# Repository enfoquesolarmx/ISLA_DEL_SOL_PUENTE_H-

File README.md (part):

# Isla del Sol — Puente H SPWM 48 V → 127 V / 60 Hz

Inversor / cargador de **puente H con modulación SPWM** para sistemas solares aislados: **48 V de batería → 127 V / 60 Hz, 1000 W**, con modo cargador de **1 kVA**.

El proyecto se publica como **referencia de estudio**: cada decisión de diseño está justificada y documentada (cálculos, hojas de datos, errores encontrados y cómo se corrigieron).

> ⚠️ **Advertencia de seguridad:** este equipo maneja corrientes altas en el lado de 48 V y **127 V AC en la salida, que pueden ser mortales**. Es un prototipo en desarrollo, no un producto certificado. Úsalo bajo tu propio riesgo y solo si tienes experiencia con electrónica de potencia.

---

*Tarjeta de potencia del puente H, prototipo de trinchera V0.1 (render 3D de KiCad). Detalles en [`hardware/puente_h/`](hardware/puente_h/README.md).*

*Tarjeta de transferencia de carga V0.1 (render 3D de KiCad): red / inversor / cargador con 5 relés y unión N–PE automática. Detalles en [`hardware/transferencia_reles/`](hardware/transferencia_reles/README.md).*

## Características principales

| Parámetro | Valor |
| --- | --- |
| Entrada | Batería de 48 V |
| Salida | 127 V / 60 Hz, 1000 W (transformador compatible 24–28 V / 120 V) |
| Modo inversor | Modulación híbrida: rama A a 24 kHz, rama B a 60 Hz |
| Modo cargador | Unipolar, ambas ramas a 24 kHz, 1 kVA |
| MOSFET | Infineon IRF100P219 (100 V), disipador Fischer SK 129 |
| Capacitores de bus | 4 × Rubycon 100ZLH820MEFC18X40 |
| Filtro de salida | ~2 mH (dispersión + inductor de ferrita E65 N87) + 4.7 µF MKP X2 |

---

## Gate drivers universales

Los módulos de gate driver son **intercambiables**: usan los mismos conectores (J1 hacia la tarjeta de control, J5 hacia el puente H) y **el mismo firmware**.

| Módulo | Tecnología | Tiempo muerto | Para qué | Estado |
| --- | --- | --- | --- | --- |
| IRS2186 | Driver de bootstrap | 500 ns | Producción, bajo costo | **Diseñado** (P9 en J1) |
| UCC21520DW | Driver aislado | 500 ns | Mejor desempeño | Diseñado |
| **TLP250 + tótem TIP41C/TIP42C** | Optoacoplador DIP + transistores TO-220 | **1 µs** | **Modo trinchera:** zonas sin acceso a componentes modernos; reparable con partes de tienda local | **V.0.1 diseñado** |
| **IR2110 + tótem TIP41C/TIP42C** | Driver de bootstrap legacy (DIP-14) + transistores TO-220 | **1 µs** | **Modo trinchera:** el driver de medio puente más fácil de conseguir o rescatar; reparable con partes de tienda local; de 1 a 5 MOSFET por posición | **V.0.1 diseñado** |

### Identificación automática del tiempo muerto (P9)

Cada módulo **declara** qué tiempo muerto necesita por la terminal **P9** de J1:

| P9 | Tiempo muerto |
| --- | --- |
| A GND | 500 ns (IRS2186, UCC21520) |
| Abierto o en falla | **1 µs** (TLP250, o cualquier duda) |

El modo seguro es el valor por defecto: un módulo legacy, un cable suelto o una soldadura fría nunca llevan a un tiempo muerto insuficiente.

### Diseño poka-yoke

El sistema está pensado para que **el error humano no pueda causar el daño**:

- Llave mecánica en la posición 8 de J5: el módulo solo entra en una posición.
- P9 abierto = 1 µs: falla segura.
- Serigrafía que dice qué hace cada módulo ("OPERACION DT TLP250=1US").
- Un solo firmware para los tres módulos: no hay versión equivocada que cargar.

---

## Contenido del repositorio

```
ISLA_DEL_SOL_PUENTE_H-/
├── README.md                                   ← este archivo
├── LICENSE.md                                  ← licencias (hardware, documentación, firmware)
├── .gitignore
├── docs/
│   ├── vision_isla_del_sol.md
│   ├── identificacion_dt_pin9.md
│   ├── modulacion_spwm.md
│   ├── decisiones_criticas.md                  ← bitácora de decisiones del arquitecto
│   ├── corte_por_hardware.md                   ← corte del PWM: SENSOR_OK, EN_HW, 74HC08
│   ├── referencia_outback_fx.md                ← estudio de referencia: OutBack FX (neutro común, unión N–PE)
│   ├── img/                                    ← diagramas (PNG, PDF y su script)
│   │   ├── README.md                           ← índice de diagramas
│   │   └── outback_fx/                         ← fotos de banco del OutBack FX
│   ├── compensacion_adaptativa_tiempo_muerto.md
│   └── sensado_corriente.md
└── hardware/
    ├── gate-drivers/
    │   ├── irs2186/
    │   │   ├── README.md
    │   │   └── GATE_DRIVER_IRS2186.kicad_pro / .kicad_sch / .kicad_pcb
    │   ├── ir2110-trinchera/
    │   │   ├── README.md
    │   │   └── GATE_DRIVER_IR2110_TOTEM.kicad_pro / .kicad_sch / .kicad_pcb
    │   ├── tlp250-trinchera/
    │   │   ├── README.md
    │   │   └── GATE_TLP_250_TOTEM_TIP.kicad_pro / .kicad_sch / .kicad_pcb
    │   └── ucc21520/
    │       ├── README.md                           ← borrador (faltan los archivos de KiCad)
    │       └── img/
    ├── puente_h/
    │   ├── README.md                               ← tarjeta de potencia
    │   ├── PUENTE_H_INV48V_REV_C_2026-10_GATE_CENTRO.kicad_pro / .kicad_sch / .kicad_pcb
    │   ├── CAPACITORES.kicad_sch                   ← hoja: banco de capacitores
    │   ├── DISIPADORES.kicad_sch                   ← hoja: disipadores
    │   ├── Heatsink_Fischer_SK129-STS_50.8mm.step  ← modelo 3D del disipador
    │   ├── Disipador_V8511Y_equiv.step             ← modelo 3D aproximado (versión anterior)
    │   ├── SSA2512_Littelfuse_Kelvin.kicad_mod     ← huella del shunt
    │   ├── SSA2512_Littelfuse.step                 ← modelo 3D del shunt
    │   ├── img/                                    ← vistas del PCB y 3D
    │   └── auditoria/
    │       ├── README.md                           ← auditoría de corriente y temperatura
    │       ├── auditoria_cobre.py · termica_componentes.py · sensibilidad.py
    │       └── resultados/                         ← figuras (.png) y resúmenes (.json)
    ├── control/
    │   ├── README.md                               ← tarjeta de control V0.1: glosario de módulos
    │   ├── ATMEGA328P_SPWM_TARJETA.kicad_pro / .kicad_sch / .kicad_pcb
    │   └── img/                                    ← esquemático, capas y vistas 3D
    ├── panel/
    │   ├── README.md                               ← panel frontal V0.2: LCD 16×2 / 20×4 I2C y 4 botones
    │   ├── PANEL_LCD_BOTONES.kicad_pro / .kicad_sch / .kicad_pcb
    │   ├── fp-lib-table + Isla_del_Sol.pretty/     ← huellas propias (ranuras M3 del LCD)
    │   └── img/                                    ← esquemático y vista del PCB
    ├── transferencia_reles/
    │   ├── README.md                               ← tarjeta de transferencia de carga V0.1
    │   ├── RELAY_TRANSFER_INV_RED.kicad_pro / .kicad_sch / .kicad_pcb
    │   ├── RELAY_TRANSFER_INV_RED.kicad_dru        ← reglas de separación (5 mm / 3 mm) para el DRC
    │   ├── 3d/                                     ← modelo 3D aproximado del relé (STEP) y su script
    │   ├── img/                                    ← esquemático, capas y vistas 3D
    │   └── auditoria/                              ← auditoría térmica a 10 A (script, mapas, informe)
    └── sensores/
        └── sensor-dc-ina-comparador/
            ├── README.md
            ├── SENSOR_DC_INA_COMPARADOR_V2.kicad_pro / .kicad_sch / .kicad_pcb   ← V0.2
            ├── SSA2512_Littelfuse_Kelvin.kicad_mod ← huella del shunt
            ├── SSA2512_Littelfuse.step             ← modelo 3D del shunt
            └── img/                                ← esquemático, PCB y evidencia del proceso
└── firmware/
    ├── aux/ISLA_AUX_PRUEBA_I2C/                ← AUX (A2): prueba del enlace I2C (maestro)
    └── critico/                                ← micro CRÍTICO (A1): SPWM, sensado, protecciones
        ├── README.md
        ├── ISLA_CRITICO/                       ← sketch de Arduino, un archivo por módulo
        │   ├── ISLA_CRITICO.ino
        │   ├── config_portadora.h / config_spwm.h
        │   ├── tabla_seno.h                    ← generado (cuarto de onda en flash)
        │   ├── spwm.h / spwm_328p.cpp          ← SPWM híbrida
        │   └── spwm_4809.cpp                   ← pendiente
        ├── herramientas/genera_tabla_seno.py
        └── pruebas/prueba_spwm.cpp             ← prueba en la PC del mismo spwm_328p.cpp
```

Próximamente: `hardware/sensores/` (sensor AC del primario).

### Documentos de sistema (`docs/`)

| Documento | Qué explica | Útil para |
| --- | --- | --- |
| [Visión: la Isla del Sol](docs/vision_isla_del_sol.md) | Por qué existe el proyecto: convertir la luz del sol en energía útil contra la cadena diaria del diésel (exploración, extracción, refinación, transporte); acceso a la electricidad como bien común; **la soberanía se construye en las trincheras** (soberanía energética: poder entender, reparar y sustituir cada pieza); hardware abierto y modo trinchera; lo que la solar también cuesta; ideas para trabajar más adelante (borrador) | Entender el propósito antes que los circuitos |
| [Identificación del tiempo muerto por P9](docs/identificacion_dt_pin9.md) | Cómo cada módulo declara su tiempo muerto (P9 a GND = 500 ns, abierto = 1 µs); soporte legacy para trincheras; costo contra beneficio; filosofía poka-yoke; llave mecánica en la posición 8; análisis de fallas; código de referencia para ATmega328 y ESP32; validación en banco | Entender la interfaz universal y escribir el firmware |
| [Modulación SPWM: bipolar, unipolar e híbrida](docs/modulacion_spwm.md) | Por qué el inversor usa modulación **híbrida** (pierna A a 24 kHz, pierna B a 60 Hz) y el cargador **unipolar**; comparación de rizo (4 : 2 : 1), consumo en vacío, pérdidas de conmutación, distorsión por tiempo muerto con módulos de 500 ns y 1 µs, modo común; ciclos de trabajo para el firmware; validación | Entender la estrategia de modulación y escribir el firmware |
| [Decisiones críticas de diseño](docs/decisiones_criticas.md) | Bitácora de decisiones del arquitecto (ADR): **por qué** se eligió cada solución, qué alternativas se descartaron y qué críticas se esperan. Entradas **DC-001 a DC-019**: cascada de alimentación 48 → 15 → 8 → 5 V ("pagamos complejidad para comprar pureza en el ADC"), XL7015 en socket mixto, protección de la entrada de 48 V, MP1584, 7805, sensado AC y de la batería, tablero de diagnóstico, holgura para capacidad médica (DC-009), reparto de tareas entre los dos ATmega con I2C y CAN (DC-010), lectura de P9 (DC-011), alimentación de los Arduino Nano (DC-012), pinza SCT-013 (DC-013), **corte del PWM por hardware** (DC-014), corriente de fuga para la V2 (DC-015), **corto circuito en AC, arranque de motores y arco** (DC-016), presupuesto de CPU/memoria y Nano Every (DC-017), **cargador híbrido y socket 328P/4809** (DC-018) y **transferencia red / inversor / cargador con 5 relés, modos INVERSOR CASA (con unión N–PE) e INVERSOR CARGA (UPS, sin unión)** (DC-019) | Entender lo que no se ve en el cobre antes de "mejorar" algo |
| [Corte del PWM por hardware](docs/corte_por_hardware.md) | Cómo el inversor se apaga en ~2–4 µs sin pedir permiso al firmware: barrera **74HC08 (AND, nunca 74HC00)**, EN_HW (D12 + switch ON/OFF + pull-down), lógica fail-safe **SENSOR_OK** (sensor ausente o cable roto = corte), jumper **J_RIESGO**, doble candado AUX/CRÍTICO; cada componente con su porqué, cálculos, firmware mínimo, serigrafía, prueba en banco y diagnóstico | Antes de soldar, probar o "mejorar" la protección del puente H |
| [Referencia industrial: OutBack FX](docs/referencia_outback_fx.md) | Estudio en banco de la etapa AC de un OutBack FX 120 V: **neutro común**, tierra de chasis pasante, **sin unión N–PE interna** (la decide el instalador, NOM 250-24 / 250-30); filtro C1 5 µF + toroide en el neutro; relé Deltrol 3PDT con clasificación HP; guía de los 4 casos de instalación; comparación con la V1 de 5 relés y sus modos **INVERSOR CASA / INVERSOR CARGA** configurados por menú y selector SW_TN | Entender la unión N–PE de la V1 y preparar la versión de bajo costo |
| [Compensación adaptativa de tiempo muerto](docs/compensacion_adaptativa_tiempo_muerto.md) | Por qué el tiempo muerto genera armónicos impares; compensación con el signo de la corriente; medición del 3er armónico con Goertzel; ajuste automático; hoja de ruta en 5 etapas | Etapa posterior: mejorar la calidad de la onda |
| [Sensado de corriente DC y AC](docs/sensado_corriente.md) | Por qué hacen falta dos sensores (bus DC y primario AC); protección por hardware; INA240 en el primario; protección del transformador contra saturación; muestreo sincronizado; calibración | Etapa posterior: base para el control avanzado |

### Módulos gate driver (`hardware/gate-drivers/`)

Todos son **gate drivers de medio puente H** (una rama: MOSFET alto + MOSFET bajo). El puente completo usa dos módulos iguales, uno por rama.

| Módulo | Documento | Archivos KiCad | Qué incluye |
| --- | --- | --- | --- |
| **IRS2186** | [README](hardware/gate-drivers/irs2186/README.md) | ✓ Esquemático (por bloques A–F con notas), PCB y proyecto | Interfaz con P9 a GND; tierras compartidas (lógica = potencia), unión única GND_K–GND con *net tie* y cómo controlar el lazo de tierra; bootstrap ES1D → R 2.2 Ω → VB con referencias; cálculo de los 500 ns; **alcance por cantidad de MOSFET** (1 IRF100P219 o hasta 2 IRF540N); opciones con tótem; lista de materiales; validación |
| **TLP250 + tótem TIP41C/TIP42C** (trinchera) | [README](hardware/gate-drivers/tlp250-trinchera/README.md) | ✓ Esquemático (por bloques A–I con **guía rápida de trinchera**: TLP250 contra TLP250H, ensamble y prueba sin MOSFET), PCB y proyecto | Propósito educativo y de supervivencia; entrada aislada; por qué 1 µs; tótem y regla de 250 nC; **evaluación de 9 transistores** (por qué TIP41/42 y no BD, Darlington, IRF540 o BC); layout; BOM; ensamble con RTV neutro; validación en 10 pasos; **registro de errores corregidos durante el diseño** |
| **UCC21520DW** | [README](hardware/gate-drivers/ucc21520/README.md) | ✓ Esquemático (por bloques), PCB y proyecto | Driver aislado de dos canales (4 A / 6 A), protección contra entradas encimadas, bootstrap; P9 a GND (500 ns). **R3 = 49.9 kΩ**: 500 ns de respaldo por hardware (el driver aplica el mayor entre firmware y R3, no la suma). **UCC21520DW** (UVLO 8 V), no la versión A (5 V) |
| **IR2110 + tótem TIP41C/TIP42C** (trinchera) | [README](hardware/gate-drivers/ir2110-trinchera/README.md) | ✓ Esquemático (por bloques A–I con **guía rápida de trinchera**: ensamble y prueba sin MOSFET), PCB y proyecto | VSS y COM separados con J5-6 a GND lógico; VDD de 5 V con 78L05; SD a VSS; tótem por canal con su desacoplo; zener en VB–VS1 y en VCC; P9 abierto (1 µs); **alcance de 1 a 5 MOSFET** y refuerzo del bootstrap; **registro de 8 errores corregidos**; BOM; validación |

### Tarjeta de potencia (`hardware/puente_h/`)

| Tarjeta | Documento | Archivos KiCad | Qué incluye |
| --- | --- | --- | --- |
| **Puente H SPWM 48 V** (REV C) | [README](hardware/puente_h/README.md) · [Auditoría](hardware/puente_h/auditoria/README.md) | ✓ Esquemático (3 hojas; raíz A3 por bloques con guía de trinchera) y PCB | 4 × IRF100P219 con disipador SK 129; pierna A a 24 kHz y B a 60 Hz; sockets universales J10/J9 con llave; banco Rubycon + cerámicos con plano partido y lazo doblado (~4 nH); shunts con Kelvin; transformador compatible 24–28 V / 120 V; salida protegida al buck (R14 + T1A, buck ≥ 80 V); **cobre de 1 oz como condición de trinchera**, con **auditoría de corriente y temperatura** (MOSFET, Rubycon y cobre) y refuerzo opcional con alambre 12 AWG; ensamble, validación, BOM y pendientes |

### Tarjeta de control (`hardware/control/`)

| Tarjeta | Documento | Archivos KiCad | Qué incluye |
| --- | --- | --- | --- |
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
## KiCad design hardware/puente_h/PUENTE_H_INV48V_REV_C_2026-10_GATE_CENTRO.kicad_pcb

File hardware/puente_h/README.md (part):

# Tarjeta de potencia: Puente H SPWM 48 V

**Isla del Sol — Puente H, prototipo V0.1** · Archivo: `PUENTE_H_INV48V_REV_C_2026-10_GATE_CENTRO` · Estado: **lista para fabricar** · pendiente de validar en banco

> ⚠️ **Seguridad:** esta tarjeta maneja hasta ~35 A en el lado de 48 V, y el transformador entrega **127 V AC, que pueden ser mortales**. Una batería de 48 V entrega cientos de amperes en un corto. Arma y prueba primero con una fuente limitada en corriente y con voltaje reducido (sección 12).

Es la tarjeta principal del inversor/cargador: contiene los cuatro MOSFET del puente H, el banco de capacitores del bus, los shunts para medir corriente y los conectores para los módulos universales (gate drivers, sensor de corriente y buck de 15 V). La lógica de control vive en otra tarjeta.

---

*Prototipo de trinchera en perspectiva (render 3D de KiCad): los cuatro IRF100P219 en sus disipadores Fischer SK 129, los Rubycon entre las dos filas de MOSFET, los films rojos de entrada, los sockets J10 y J9 para los gate drivers, J3 para el sensor DC y la salida J8 con su resistencia fusible R14.*

---

## 1. Características

| Parámetro | Valor |
| --- | --- |
| Entrada | Batería de 48 V (bus de ~42 a ~60 V) |
| Potencia | 1000 W como inversor; 1 kVA como cargador |
| Salida | Primario del transformador de 60 Hz (rango compatible 24–28 V / 120 V, sección 9) |
| Topología | Puente H completo: dos piernas, un MOSFET alto y uno bajo en cada una |
| MOSFET | 4 × Infineon **IRF100P219** (100 V, 1.4 mΩ típico), TO-247 vertical |
| Disipadores | 4 × Fischer **SK 129 50.8 STS** (5.3 °C/W), soldados a la tarjeta |
| Modulación (inversor) | **Híbrida:** pierna A a 24 kHz, pierna B a 60 Hz |
| Modulación (cargador) | **Unipolar:** las dos piernas a 24 kHz |
| Capacitores de bus | 4 × Rubycon **100ZLH820MEFC18X40** + 4 × 10 µF + 4 × 4.7 µF X7R + film 1 µF |
| Medición de corriente | Shunts Littelfuse SSA2512 de 1 mΩ en el retorno de la batería (1 a 3 piezas) |
| Cobre | **2 capas, 1 oz (35 µm)**: es la condición de diseño, porque es lo que se consigue en trinchera |
| Tamaño de la tarjeta | ~166 × 140 mm |

---

## 2. Archivos

| Archivo | Contenido |
| --- | --- |
| `PUENTE_H_INV48V_REV_C_2026-10_GATE_CENTRO.kicad_pro` | Proyecto de KiCad 9 (ábrelo para cargar todo) |
| `PUENTE_H_INV48V_REV_C_2026-10_GATE_CENTRO.kicad_sch` | Esquemático principal (hoja raíz A3 por bloques A–I, KiCad 9) |
| `CAPACITORES.kicad_sch` | Hoja jerárquica: banco de capacitores del bus (antes `CAPASITORES.kicad_sch`) |
| `DISIPADORES.kicad_sch` | Hoja jerárquica: disipadores (antes `untitled.kicad_sch`) |
| `ESTUDIOS.kicad_sch` | Hoja jerárquica sin conexiones: las tres láminas de estudio (red de compuerta y comparación de MOSFET), sección 6.1 |
| `PUENTE_H_INV48V_REV_C_2026-10_GATE_CENTRO.kicad_pcb` | Layout |
| `Heatsink_Fischer_SK129-STS_50.8mm.step` | Modelo 3D del disipador Fischer SK 129 50.8 STS (hecho con las coordenadas de la huella oficial de KiCad) |
| `Disipador_V8511Y_equiv.step` | Modelo 3D aproximado de un disipador equivalente (versión anterior, ya no se usa en el layout) |
| `SSA2512_Littelfuse_Kelvin.kicad_mod` · `SSA2512_Littelfuse.step` | Huella y modelo 3D del shunt (los mismos que en la carpeta del sensor) |
| `auditoria/` | Auditoría de corriente y temperatura del layout: herramientas, figuras y [README](auditoria/README.md) |

---

## 3. Cómo está organizada

*Hoja raíz (KiCad 9, A3) por bloques, pensada para quien arma y repara:*

| Bloque | Contenido |
| --- | --- |
| **A** | Entrada de batería (Faston J5/J6 = BAT+, J1/J2 = BAT−) |
| **B** | Shunts R16/R28/R17 con sus Kelvin NT5/NT6 y el sensor J3 |
| **C** | Pierna A (VS1, 24 kHz): Q1/Q2 con su red de compuerta, Kelvin y bornes J24/J27 |
| **D** | Pierna B (VS2, 60 Hz): Q3/Q4, igual que la A, con bornes J23/J22 |
| **E** | Sockets J10 (A) y J9 (B) de los gate drivers |
| **F** | Alimentación **15V_GA** (J7, LED D6) y **15V_GB** (J4, LED D5) |
| **G** | Salida J8 al buck, con R14 |
| **H** | Hojas jerárquicas CAPACITORES, DISIPADORES y ESTUDIOS |
| **I** | Notas al día y guía rápida de trinchera |

*Cada bloque lleva su nota: qué hace, qué medir y qué pasa si algo va mal.*

```
 BATERÍA 48 V
   (+)──Faston J5, J6────────────── plano 48 V (F.Cu, mitad inferior) ──┬── Q1 (alto A) ── Q3 (alto B)
   (−)──Faston J1, J2── GND_IN ── shunts R16/R28/R17 ── plano GND ──────┴── Q2 (bajo A) ── Q4 (bajo B)
                                     │ Kelvin (NT5/NT6)
                                     └── J3 → módulo SENSOR_DC_INA_COMPARADOR

   Pierna A (24 kHz): Q1 + Q2 → VS1 → bornes J24 + J27 ─┐
                                                        ├── transformador (dos cables en paralelo por lado)
   Pierna B (60 Hz):  Q3 + Q4 → VS2 → bornes J23 + J22 ─┘

   Fila central: C1 C2 (pierna A) · J10 (gate driver A) · C3 C4 (pierna B) · J9 (gate driver B)
   J8: salida de 48 V protegida (R14) para el buck de 15 V de la tarjeta de control
```

*Vista 3D de la cara de componentes. Arriba, los MOSFET bajos (Q2, Q4) con sus disipadores; en medio, los cuatro Rubycon con los cerámicos de 4.7 µF y los sockets J10 y J9; abajo, los MOSFET altos (Q1, Q3). A la izquierda, los Faston de batería (NEG − / POS +), los shunts y los films C10 (MKS) y C9 (MKP). Las franjas claras de arriba y abajo son las tiras sin máscara del bus.*

*Vista del editor de PCB de KiCad, con las dos capas encendidas. A la izquierda, la entrada de batería (NEG − arriba, POS + abajo), los shunts y los films C9/C10. En el centro, las dos piernas: los MOSFET bajos con sus disipadores arriba, la fila de Rubycon en medio, sobre la frontera GND / 48 V, y los MOSFET altos abajo. J10 (pierna A, "24K") y J9 (pierna B, "60HZ") son los sockets de los gate drivers. Abajo a la izquierda, R14 y la salida J8 al buck.*

| Zona | Qué hay |
| --- | --- |
| Izquierda | Entrada de batería (Faston), shunts, conector del sensor J3, films C9 y C10, salida J8 al buck |
| Centro izquierda | Pierna A: Q2 arriba (bajo), Q1 abajo (alto), con sus disipadores; C1 y C2 en medio |
| Centro | J10, el socket del gate driver de la pierna A |
| Centro derecha | Pierna B: Q4 arriba (bajo), Q3 abajo (alto); C3 y C4 en medio |
| Derecha | J9, el socket del gate driver de la pierna B |

---

## 4. Conectores

| Ref. | Tipo | Señales | Notas |
| --- | --- | --- | --- |
| J5, J6 | Faston 6.35 mm (TE 63823) | **48 V** de batería | Dos en paralelo, ~15 A cada uno a plena carga. Confirmar la corriente por terminal en la hoja de datos de TE. |
| J1, J2 | Faston 6.35 mm | **GND_IN** (negativo de batería) | Antes de los shunts |
| J24, J27 | Borne M3 con vías | **VS1** | Dos cables en paralelo a una terminal del transformador |
| J23, J22 | Borne M3 con vías | **VS2** | Dos cables en paralelo a la otra terminal |
| J10 | Socket 1 × 9, 2.54 mm | Gate driver de la pierna A | Pinout en la tabla siguiente |
| J9 | Socket 1 × 9, 2.54 mm | Gate driver de la pierna B | Mismo pinout |
| J7 | JST EH 2 pines | **15V_GA** + GND | Alimentación del gate driver A (J10) **solamente** (LED D6) |
| J4 | JST EH 2 pines | **15V_GB** + GND | Alimentación del gate driver B (J9) y del sensor J3 (LED D5) |
| J3 | Header 1 × 6, 2.54 mm | 1 GND · 2 IN+ · 3 IN− · 4 GND · 5 **llave** · 6 15V_GB | Módulo SENSOR_DC_INA_COMPARADOR (sensado Kelvin del shunt) |
| J8 | JST EH 2 pines | 48 V protegido + GND | Al buck de 15 V de la tarjeta de control, a través de R14 (sección 10) |

**Pinout de J10 y J9** (igual al J5 de todos los módulos gate driver; ver `docs/identificacion_dt_pin9.md`):

| Pin | Pierna A (J10) | Pierna B (J9) | Función |
| --- | --- | --- | --- |
| 1 | HO_A | HO_B | Gate del MOSFET alto |
| 2 | VS1_k | VS2_k | Retorno Kelvin del MOSFET alto |
| 3 | NC | NC | — |
| 4 | GND_KELVIN_A | GND_KELVIN_B | Retorno Kelvin del MOSFET bajo |
| 5 | LO_A | LO_B | Gate del MOSFET bajo |
| 6 | GND | GND | Tierra de potencia |
| 7 | 15V_GA | 15V_GB | Alimentación del módulo (cada pierna con su propio 15 V) |
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
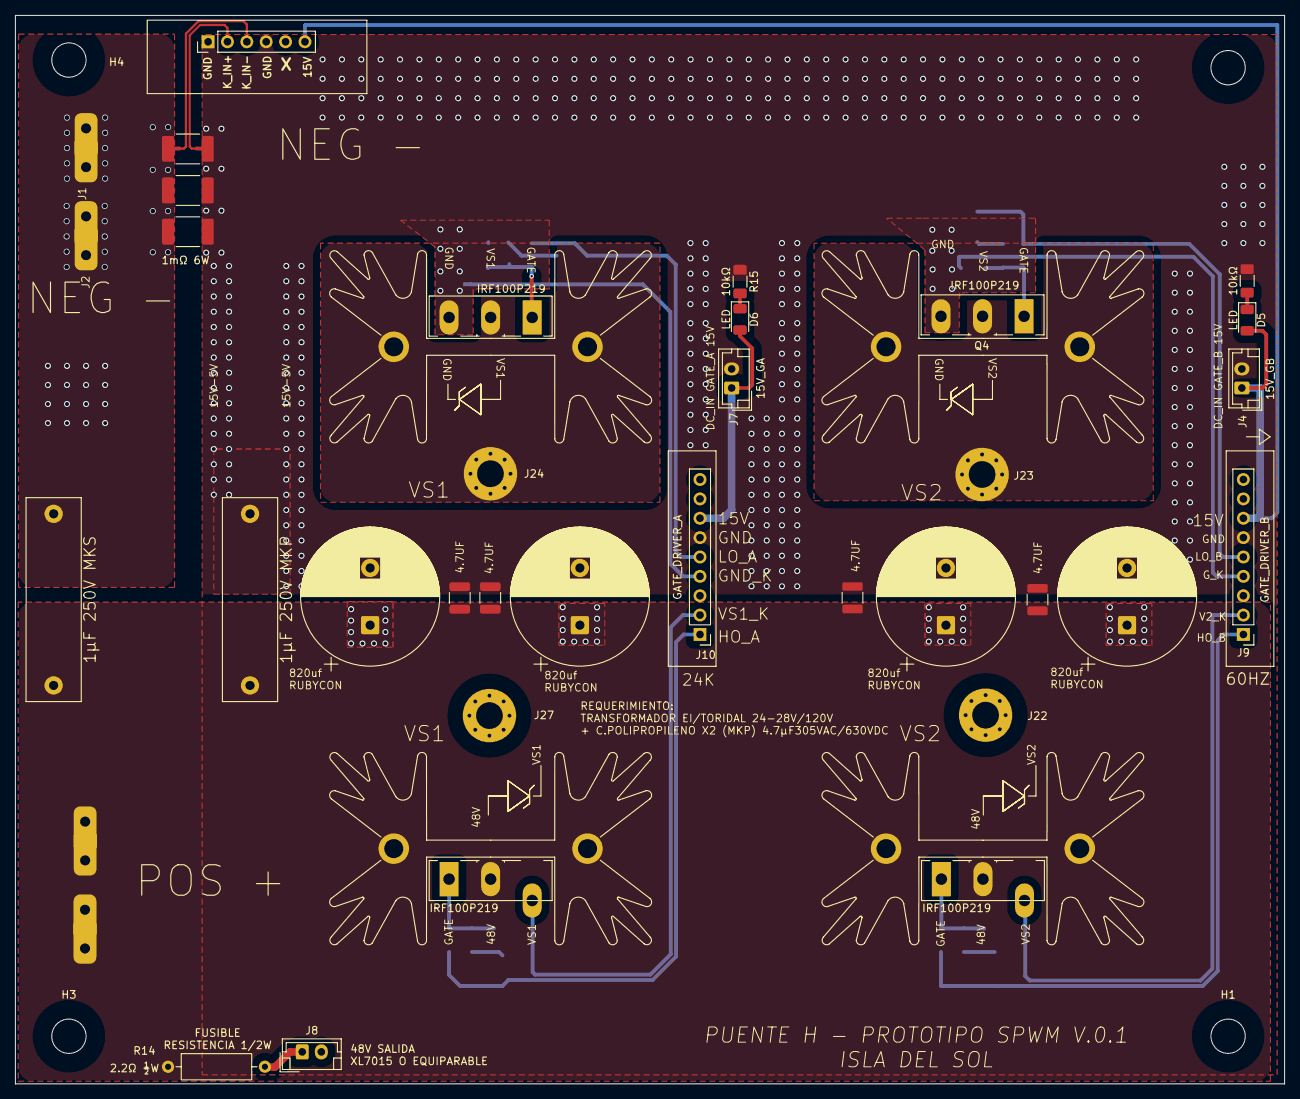
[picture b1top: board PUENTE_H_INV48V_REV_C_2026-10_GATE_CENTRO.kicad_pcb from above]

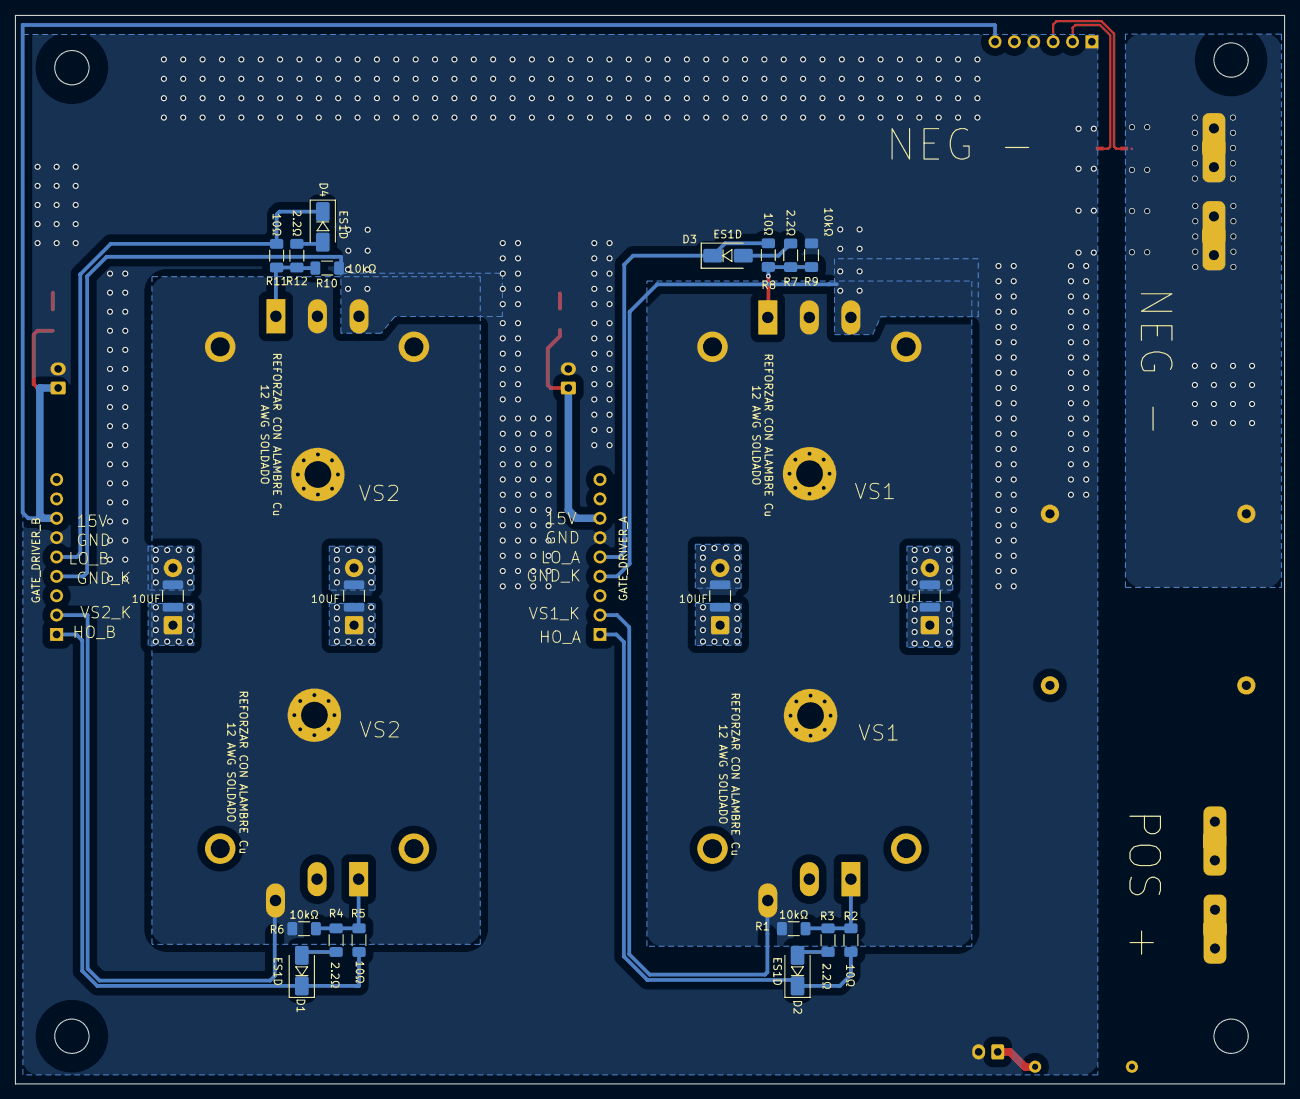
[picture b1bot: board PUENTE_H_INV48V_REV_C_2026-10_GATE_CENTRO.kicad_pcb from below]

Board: 2 copper layers, 166.4 x 140.1 mm, 70 parts (24 on the bottom side), 28 nets.

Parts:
C1, C2, C3, C4: 820µF 100V Rubycon ZLH; CP_Radial_D18.0mm_P7.50mm
C5, C6, C7, C8: 10µF 100V X7R; C_1210_3225Metric
C9: 1µF 250V MKP; C_Rect_L26.5mm_W7.0mm_P22.50mm_MKS4
C10: 1µF 250V MKS; C_Rect_L26.5mm_W7.0mm_P22.50mm_MKS4
C11, C12, C13, C14: 4.7µF 100V X7R; C_1210_3225Metric
D1, D2, D3, D4: ES1D; D_SMA
D5, D6: LED; LED_1206_3216Metric
H1, H2, H3, H4: MountingHole; MountingHole_4.5mm
HS5: DISIPADOR_1; Heatsink_Fischer_SK129-STS_42x25mm_2xDrill2.5mm
HS6: DISIPADOR_3; Heatsink_Fischer_SK129-STS_42x25mm_2xDrill2.5mm
HS7: DISIPADOR_2; Heatsink_Fischer_SK129-STS_42x25mm_2xDrill2.5mm
HS8: DISIPADOR_4; Heatsink_Fischer_SK129-STS_42x25mm_2xDrill2.5mm
J1, J2: BAT− (GND_IN); Faston 63823
J3: SENSOR_DC (llave en 5); PinHeader_1x06_P2.54mm_Vertical
J4: 15V_GB; JST_EH_B2B-EH-A_1x02_P2.50mm_Vertical
J5, J6: BAT+ (48V); Faston 63823
J7: 15V_GA; JST_EH_B2B-EH-A_1x02_P2.50mm_Vertical
J8: 48V → BUCK (≥80 V); JST_EH_B2B-EH-A_1x02_P2.50mm_Vertical
J9: GATE_DRIVER_B; PinHeader_1x09_P2.54mm_Vertical
J10: GATE_DRIVER_A; PinHeader_1x09_P2.54mm_Vertical
J22, J23: VS2; MountingHole_3.5mm_Pad_Via
J24, J27: VS1; MountingHole_3.5mm_Pad_Via
NT1, NT2, NT3, NT4, NT5, NT6: Kelvin; NetTie-2_SMD_Pad0.5mm
Q1, Q2, Q3, Q4: IRF100P219; TO-247-3_Vertical
R1, R6, R9, R10, R13, R15: 10kΩ; R_1206_3216Metric_Pad1.30x1.75mm_HandSolder
R2, R5, R8, R11: 10Ω; R_1206_3216Metric_Pad1.30x1.75mm_HandSolder
R3, R4, R7, R12: 2.2Ω; R_1206_3216Metric_Pad1.30x1.75mm_HandSolder
R14: 2.2Ω ½W; R_Axial_DIN0309_L9.0mm_D3.2mm_P12.70mm_Horizontal
R16: 1mΩ 6W (Kelvin, siempre); SSA2512_Littelfuse_Kelvin
R17: 1mΩ 6W (opcional); SSA2512_Littelfuse_Kelvin
R28: 1mΩ 6W; SSA2512_Littelfuse_Kelvin

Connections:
15V_GA: D6.2 (A), J7.1, J10.7
15V_GB: D5.2 (A), J3.6, J4.1, J9.7
48V: C1.1, C2.1, C3.1, C4.1, C5.1, C6.1, C7.1, C8.1, C9.1, C10.1, C11.1, C12.1, C13.1, C14.1, HS5.1, HS7.1, J5.1, J6.1, Q1.2 (D), Q3.2 (D), R14.1
GND: C1.2, C2.2, C3.2, C4.2, C5.2, C6.2, C7.2, C8.2, C9.2, C11.2, C12.2, C13.2, C14.2, J3.1, J3.4, J4.2, J7.2, J8.2, J9.6, J10.6, NT1.2, NT2.2, NT5.2, Q2.3 (S), Q4.3 (S), R9.2, R10.2, R13.1, R15.1, R16.2, R17.2, R28.2
GND_IN: C10.2, J1.1, J2.1, NT6.2, R16.1, R17.1, R28.1
GND_KELVIN_A: J10.4, NT2.1
GND_KELVIN_B: J9.4, NT1.1
HO_A: D2.1 (K), J10.1, R2.1
HO_B: D1.1 (K), J9.1, R5.1
IN+ (Kelvin): J3.2, NT5.1
IN- (Kelvin): J3.3, NT6.1
LO_A: D3.1 (K), J10.5, R8.1
LO_B: D4.1 (K), J9.5, R11.1
unnamed: D1.2 (A), R4.1
unnamed: D2.2 (A), R3.1
unnamed: D3.2 (A), R7.1
unnamed: D4.2 (A), R12.1
unnamed: D5.1 (K), R13.2
unnamed: D6.1 (K), R15.2
unnamed: J8.1, R14.2
unnamed: Q1.1 (G), R1.1, R2.2, R3.2
unnamed: Q2.1 (G), R7.2, R8.2, R9.1
unnamed: Q3.1 (G), R4.2, R5.2, R6.1
unnamed: Q4.1 (G), R10.1, R11.2, R12.2
VS1: HS6.1, J24.1, J27.1, NT4.2, Q1.3 (S), Q2.2 (D), R1.2
VS1_k: J10.2, NT4.1
VS2: HS8.1, J22.1, J23.1, NT3.2, Q3.3 (S), Q4.2 (D), R6.2
VS2_k: J9.2, NT3.1

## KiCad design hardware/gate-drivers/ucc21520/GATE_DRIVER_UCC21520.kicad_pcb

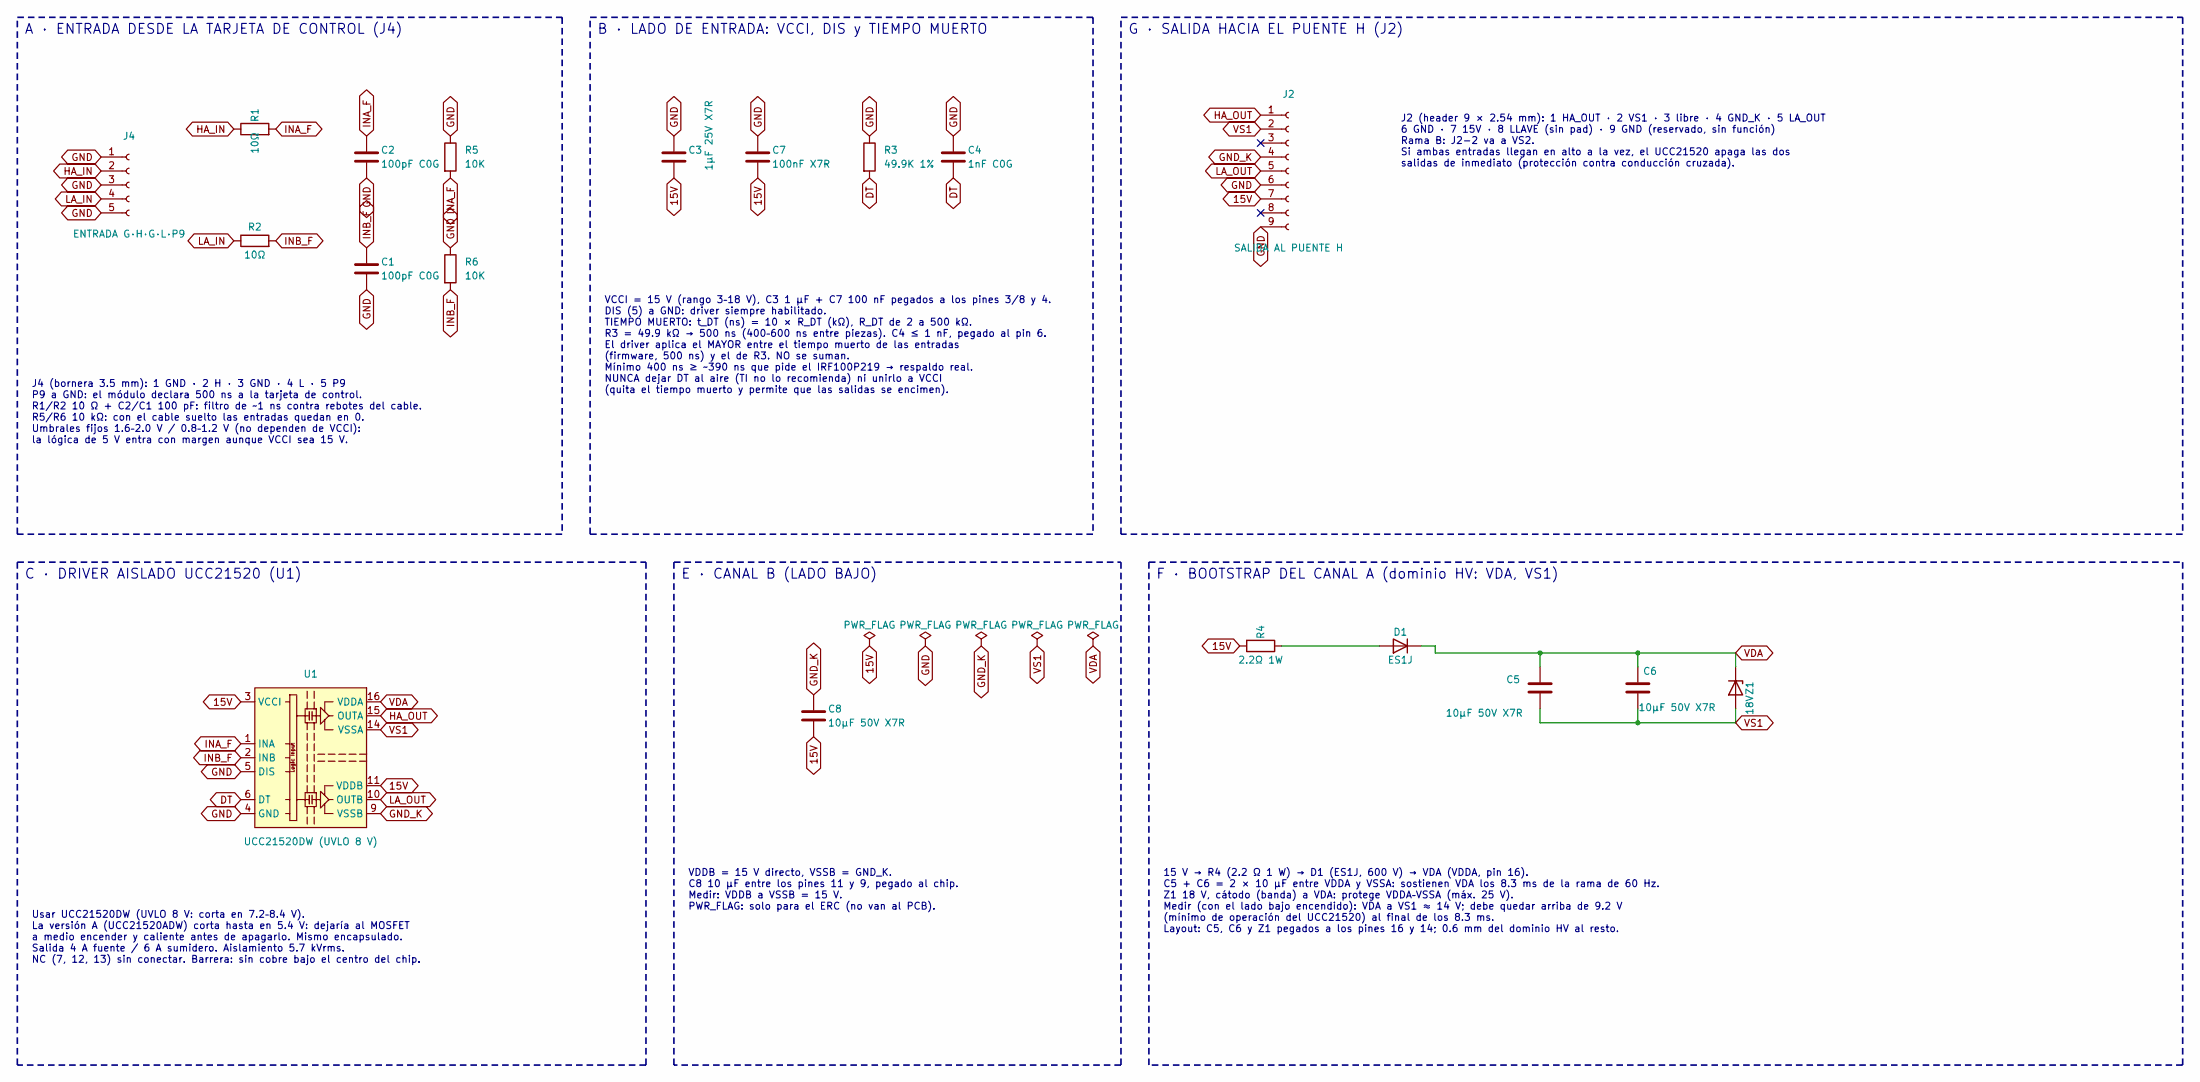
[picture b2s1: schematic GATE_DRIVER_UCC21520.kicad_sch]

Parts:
C1, C2: 100pF C0G; C_1206_3216Metric
C3: 1µF 25V X7R; C_1206_3216Metric
C4: 1nF C0G; C_1206_3216Metric
C5, C6, C8: 10µF 50V X7R; C_1206_3216Metric
C7: 100nF X7R; C_1206_3216Metric
D1: ES1J; D_SMA
J2: SALIDA AL PUENTE H; PinHeader_1x09_P2.54mm_Vertical
J4: ENTRADA G·H·G·L·P9; PhoenixContact_SPT_1.5_5-H-3.5_1x05_P3.5mm_Horizontal
R1, R2: 10Ω; R_1206_3216Metric
R3: 49.9K 1%; R_1206_3216Metric
R4: 2.2Ω 1W; R_1210_3225Metric_Pad1.30x2.65mm_HandSolder
R5, R6: 10K; R_1206_3216Metric
U1: UCC21520DW (UVLO 8 V); SOIC-16W_7.5x10.3mm_P1.27mm
Z1: 18V; D_SMA

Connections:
15V: C3.2, C7.2, C8.2, J2.7, R4.2, U1.3 (VCCI), U1.8 (VCCI), U1.11 (VDDB)
DT: C4.2, R3.2, U1.6 (DT)
GND: C1.2, C2.2, C3.1, C4.1, C7.1, J2.6, J2.9, J4.1, J4.3, J4.5, R3.1, R5.1, R6.1, U1.4 (GND), U1.5 (DIS)
GND_K: C8.1, J2.4, U1.9 (VSSB)
HA_IN: J4.2, R1.1
HA_OUT: J2.1, U1.15 (OUTA)
INA_F: C2.1, R1.2, R5.2, U1.1 (INA)
INB_F: C1.1, R2.2, R6.2, U1.2 (INB)
LA_IN: J4.4, R2.1
LA_OUT: J2.5, U1.10 (OUTB)
unnamed: D1.2 (A), R4.1
VDA: C5.2, C6.2, D1.1 (K), U1.16 (VDDA), Z1.1 (K)
VS1: C5.1, C6.1, J2.2, U1.14 (VSSA), Z1.2 (A)

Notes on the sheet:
VCCI = 15 V (rango 3–18 V), C3 1 µF + C7 100 nF pegados a los pines 3/8 y 4. DIS (5) a GND: driver siempre habilitado. TIEMPO MUERTO: t_DT (ns) = 10 × R_DT (kΩ), R_DT de 2 a 500 kΩ. R3 = 49.9 kΩ → 500 ns (400–600 ns entre piezas). C4 ≤ 1 nF, pegado al pin 6. El driver aplica el MAYOR entre el tiemp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
15 V → R4 (2.2 Ω 1 W) → D1 (ES1J, 600 V) → VDA (VDDA, pin 16). C5 + C6 = 2 × 10 µF entre VDDA y VSSA: sostienen VDA los 8.3 ms de la rama de 60 Hz. Z1 18 V, cátodo (banda) a VDA: protege VDDA–VSSA (máx. 25 V). Medir (con el lado bajo encendido): VDA a VS1 ≈ 14 V; debe quedar arriba de 9.2 V (mínimo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
B · LADO DE ENTRADA: VCCI, DIS y TIEMPO MUERTO
A · ENTRADA DESDE LA TARJETA DE CONTROL (J4)
J2 (header 9 × 2.54 mm): 1 HA_OUT · 2 VS1 · 3 libre · 4 GND_K · 5 LA_OUT 6 GND · 7 15V · 8 LLAVE (sin pad) · 9 GND (reservado, sin función) Rama B: J2-2 va a VS2. Si ambas entradas llegan en alto a la vez, el UCC21520 apaga las dos salidas de inmediato (protección contra conducción cruzada).
F · BOOTSTRAP DEL CANAL A (dominio HV: VDA, VS1)
E · CANAL B (LADO BAJO)
VDDB = 15 V directo, VSSB = GND_K. C8 10 µF entre los pines 11 y 9, pegado al chip. Medir: VDDB a VSSB = 15 V. PWR_FLAG: solo para el ERC (no van al PCB).
C · DRIVER AISLADO UCC21520 (U1)
J4 (bornera 3.5 mm): 1 GND · 2 H · 3 GND · 4 L · 5 P9 P9 a GND: el módulo declara 500 ns a la tarjeta de control. R1/R2 10 Ω + C2/C1 100 pF: filtro de ~1 ns contra rebotes del cable. R5/R6 10 kΩ: con el cable suelto las entradas quedan en 0. Umbrales fijos 1.6–2.0 V / 0.8–1.2 V (no dependen de VCCI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
Usar UCC21520DW (UVLO 8 V: corta en 7.2–8.4 V). La versión A (UCC21520ADW) corta hasta en 5.4 V: dejaría al MOSFET a medio encender y caliente antes de apagarlo. Mismo encapsulado. Salida 4 A fuente / 6 A sumidero. Aislamiento 5.7 kVrms. NC (7, 12, 13) sin conectar. Barrera: sin cobre bajo el centr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
G · SALIDA HACIA EL PUENTE H (J2)

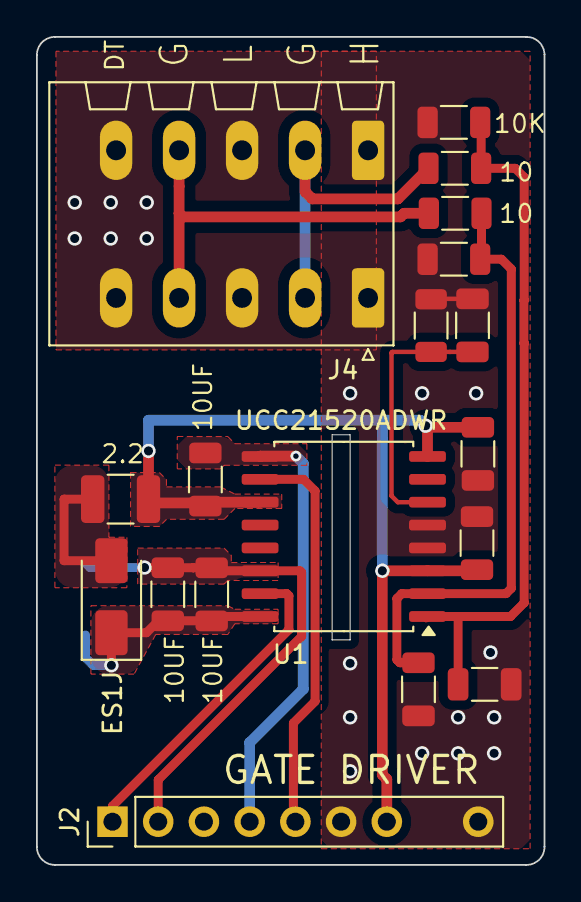
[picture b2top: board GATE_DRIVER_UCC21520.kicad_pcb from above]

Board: 2 copper layers, 28.2 x 46.0 mm, 19 parts (1 on the bottom side), 13 nets.

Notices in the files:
README.md:
Licencia:
- **Hardware** (archivos de KiCad, Gerbers): CERN-OHL-S v2
- **Documentación**: CC BY-SA 4.0
- **Firmware**: MIT
Ver [`LICENSE.md`](LICENSE.md).
Las hojas de datos de los fabricantes no se incluyen en el repositorio por derechos de autor; los documentos citan la fuente de cada dato.
hardware/puente_h/README.md:
Hardware bajo licencia CERN-OHL-S v2; documentación CC BY-SA 4.0 (ver `LICENSE.md` en la raíz).
